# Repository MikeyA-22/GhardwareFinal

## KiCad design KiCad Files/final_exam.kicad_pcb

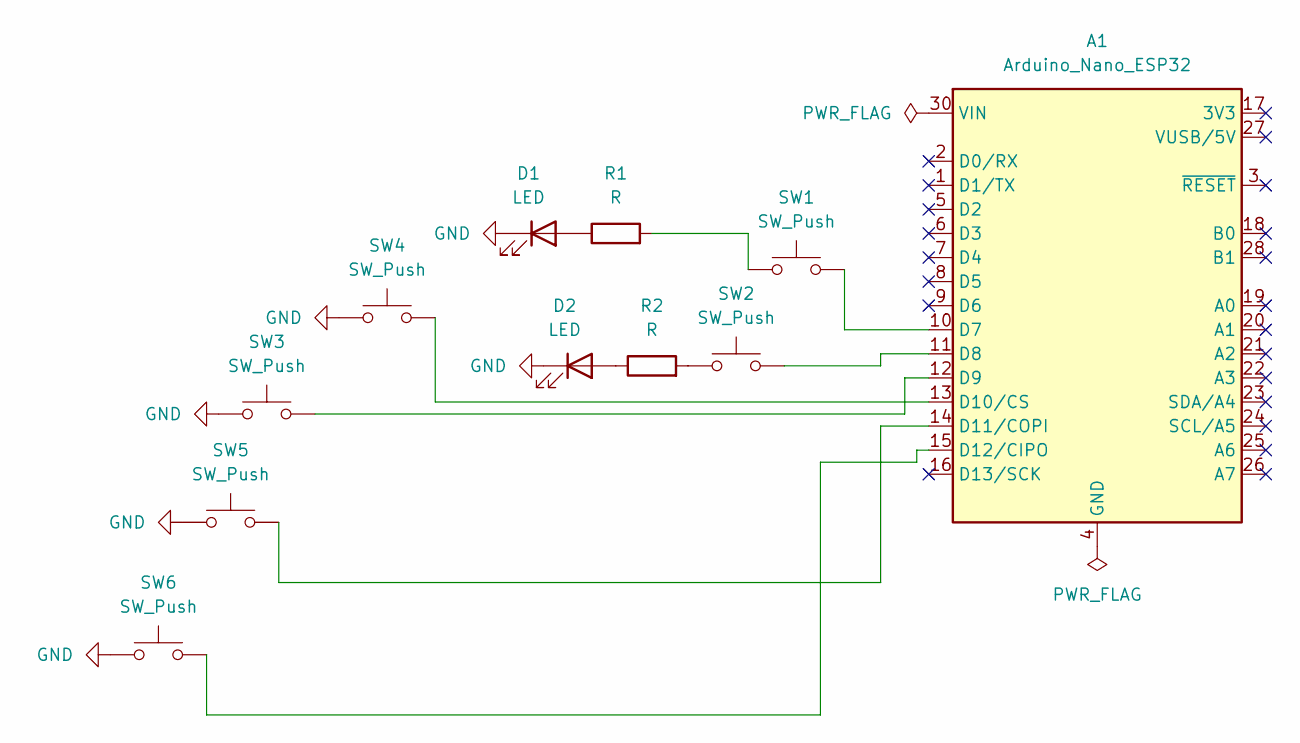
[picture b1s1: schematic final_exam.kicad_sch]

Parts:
A1: Arduino_Nano_ESP32; Arduino_Nano
D1, D2: LED; LED_D4.0mm
R1, R2: R; R_Axial_DIN0204_L3.6mm_D1.6mm_P7.62mm_Horizontal
SW1, SW2, SW3, SW4, SW5, SW6: SW_Push; SW_PUSH_6mm

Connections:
GND: D1.1 (K), D2.1 (K), SW3.1, SW4.1, SW5.1, SW6.1
unnamed: A1.10 (D7), SW1.2
unnamed: A1.11 (D8), SW2.2
unnamed: A1.12 (D9), SW3.2
unnamed: A1.13 (D10/CS), SW4.2
unnamed: A1.14 (D11/COPI), SW5.2
unnamed: A1.15 (D12/CIPO), SW6.2
unnamed: A1.4 (GND), A1.29 (GND)
unnamed: D1.2 (A), R1.1
unnamed: D2.2 (A), R2.1
unnamed: R1.2, SW1.1
unnamed: R2.2, SW2.1

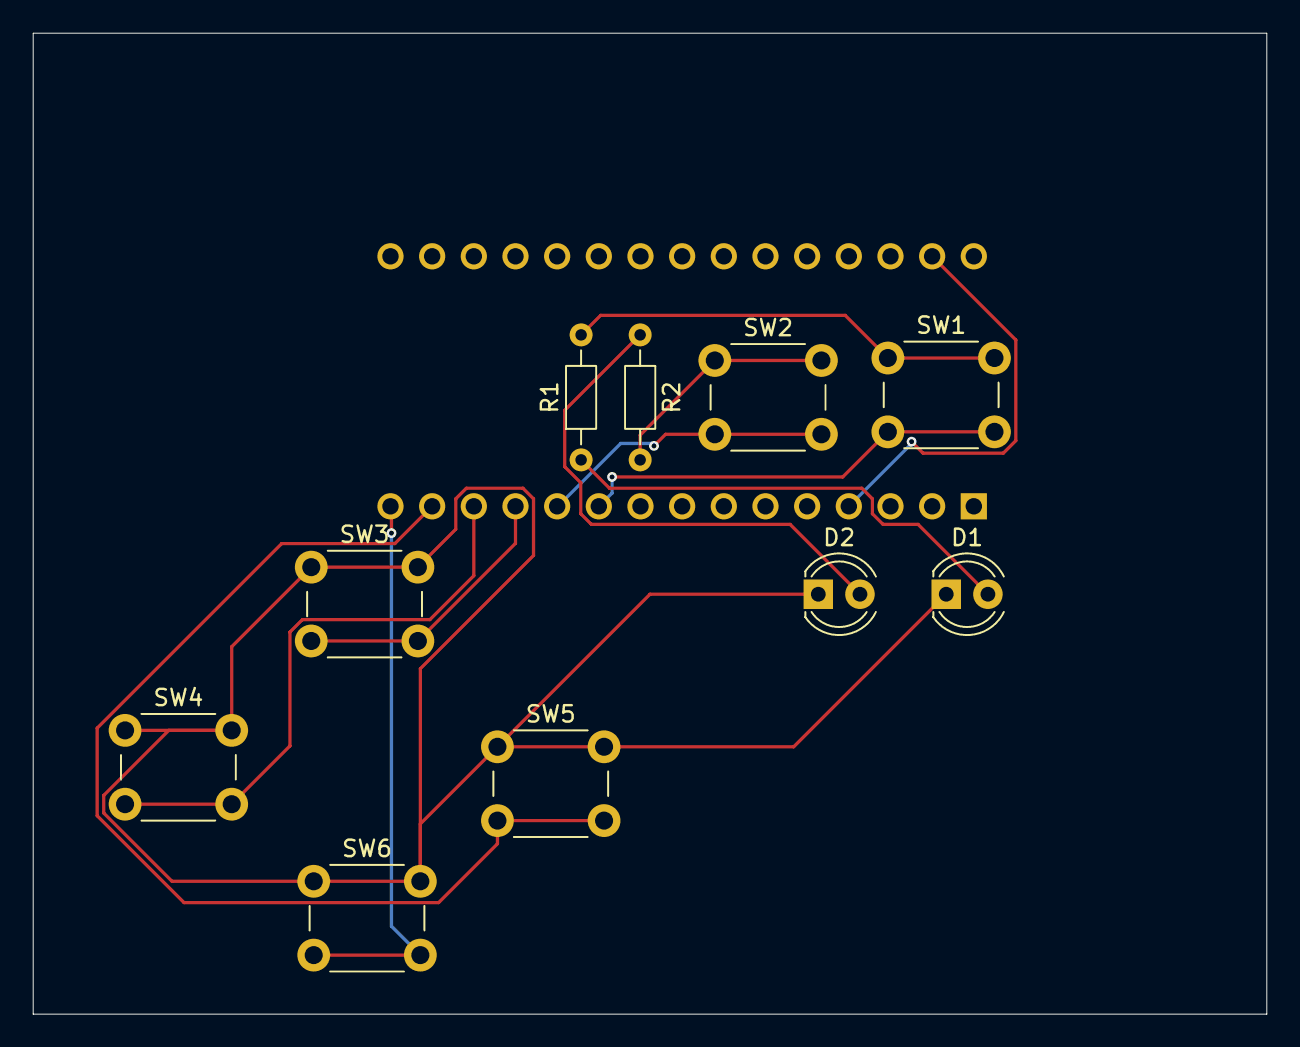
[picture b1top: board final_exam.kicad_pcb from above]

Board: 2 copper layers, 75.2 x 59.8 mm, 11 parts (1 on the bottom side), 12 nets.

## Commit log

2026-04-19 final practical submission
2026-04-19 kicad files and some modifications
